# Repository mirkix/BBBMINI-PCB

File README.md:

# BBBMINI-PCB

## License

<br /><span xmlns:dct="http://purl.org/dc/terms/" property="dct:title">BBBmini</span> by <a xmlns:cc="http://creativecommons.org/ns#" href="https://github.com/mirkix" property="cc:attributionName" rel="cc:attributionURL">Mirko Denecke</a> is licensed under a <a rel="license" href="http://creativecommons.org/licenses/by-sa/4.0/">Creative Commons Attribution-ShareAlike 4.0 International License</a>.

UNLESS OTHERWISE MUTUALLY AGREED TO BY THE PARTIES IN WRITING, LICENSOR OFFERS THE WORK AS-IS AND MAKES NO REPRESENTATIONS OR WARRANTIES OF ANY KIND CONCERNING THE WORK, EXPRESS, IMPLIED, STATUTORY OR OTHERWISE, INCLUDING, WITHOUT LIMITATION, WARRANTIES OF TITLE, MERCHANTABILITY, FITNESS FOR A PARTICULAR PURPOSE, NONINFRINGEMENT, OR THE ABSENCE OF LATENT OR OTHER DEFECTS, ACCURACY, OR THE PRESENCE OF ABSENCE OF ERRORS, WHETHER OR NOT DISCOVERABLE. SOME JURISDICTIONS DO NOT ALLOW THE EXCLUSION OF IMPLIED WARRANTIES, SO SUCH EXCLUSION MAY NOT APPLY TO YOU. EXCEPT TO THE EXTENT REQUIRED BY APPLICABLE LAW, IN NO EVENT WILL LICENSOR BE LIABLE TO YOU ON ANY LEGAL THEORY FOR ANY SPECIAL, INCIDENTAL, CONSEQUENTIAL, PUNITIVE OR EXEMPLARY DAMAGES ARISING OUT OF THIS LICENSE OR THE USE OF THE WORK, EVEN IF LICENSOR HAS BEEN ADVISED OF THE POSSIBILITY OF SUCH DAMAGES.

## Changelog

Rev 1.5
* Add second I2C port
* Add current and voltage sensing
* Fix HC-SR04 voltage divider

Rev 1.4
* Add connector for Ultra Sonic Range Finder HC-SR04.
* Add 5V pin to P10 (GPS / UART4)
* Add 5V pin to P4 (RC Input)
* Add voltage divider to P4 (RC Input) pin RC_IN (RCIN) to connect 5V signals to RC_IN (RCIN)
* Add MPU-9250 interrupt singal to PRU0

Rev 1.2
* Initial commit

## BOM

### PCB

You can order BBBmini PCBs from OSHPARK https://oshpark.com/shared_projects/CtVQp1YO .

This is an example how you can get 10 BBBMINI-PCBs for less than 30$ at Shenthen2u.

Goto http://www.shenzhen2u.com/PCB 

Upload [bbbmini.zip](kicad/gerber/bbbmini.zip) to supplier.

Finish your order.

### IMU MPU-9250

Search for GY-9250 or MPU-9250 at [aliexpress](http://www.aliexpress.com/wholesale?SearchText=gy-9250)

### Baro MS5611

Search for GY-63 or MS5611 at [aliexpress](http://www.aliexpress.com/wholesale?SearchText=gy-63)

### Rangefinder HC-SR04

Search for HC-SR04, there are a lot of sellers.

## Connector

### P1 & P2
* 2.54mm pin header 3 x 12 straight or 90°
* 12 x RC out 3.3V

### P3
* 2.54 mm pin header 1 x 2 straight
* Close this jumper to connect 5V BBBMINI power supply to P1 / P2 RC out 5V

### P4 
* 2.54 mm pin header 1 x 4 straight
* RC receiver input. 
* For 5V RCIN signal R4 = 1kOhm and R5 = 2kOhm.
* For 3.3V RCIN signal R4 = 0Ohm / bridged and R5 = open / not equipped.

### P5
* 2.54mm pin header female 1 x 10 straight
* MPU-9250 breakout board

### P6
* 2.54mm pin header female 1 x 7 straight
* MS5611 breakout board

### P7
* 2.54mm pin header 1 x 5 straight
* UART4 port
* RX and TX 3.3V signals

### P8
* 2.54mm pin header 2 x 23 straight
* BeagleBone connector, pin header has to soldered on the back of the BBBMINI-PCB

### P9
* 2.54mm pin header 2 x 23 straight
* BeagleBone connector, pin header has to soldered on the back of the BBBMINI-PCB

### P10
* 2.54mm pin header 1 x 5 straight
* UART5 port (GPS)
* RX and TX 3.3V signals

### P11
* 2.54mm pin header 1 x 2 straight
* Connector for power supply. Use this connector to power the BeagleBone Black and BBBMIN-PCB. You can also use the BeagleBone Black power plug to power the BeagleBone Black and BBBMINI-PCB.

### P12
* 2.54mm pin header 1 x 7 straight
* External SPI Bus connector for additional hardware. 
* MOSI, MISO, SCLK and CS 3.3V

### P13
* 2.54mm pin header 1 x 2 straight
* CAN Bus interface

### P14
* 2.54mm pin header 1 x 2 straight
* Close this jumper to enable 120Ohm CAN Bus resistor.

### P15
* 2.54mm pin header 1 x 5 straight
* External I2C Bus  connector for additional hardware.
* SDA and SCL 3.3V

### P16
* 2.54mm pin header 1 x 3 straight
* Additional RC_1 ESC out connector for X-Quad configuration.
* RC_1 out 3.3V

### P17
* 2.54mm pin header 1 x 3 straight
* Additional RC_3 ESC out connector for X-Quad configuration.
* RC_3 out 3.3V

### P18
* 2.54mm pin header 1 x 3 straight
* Additional RC_4 ESC out connector for X-Quad configuration.
* RC_4 out 3.3V

### P19
* 2.54mm pin header 1 x 4 straight
* Ultrasonic Range Finder connector
* Connect HC-SR04 Range Finder here.  

### P20
* 2.54mm pin header 1 x 5 straight
* External I2C Bus  connector for additional hardware.
* SDA and SCL 3.3V

### P21
* 2.54mm pin header 1 x 3 straight
* Current and voltage sensing via Power Module

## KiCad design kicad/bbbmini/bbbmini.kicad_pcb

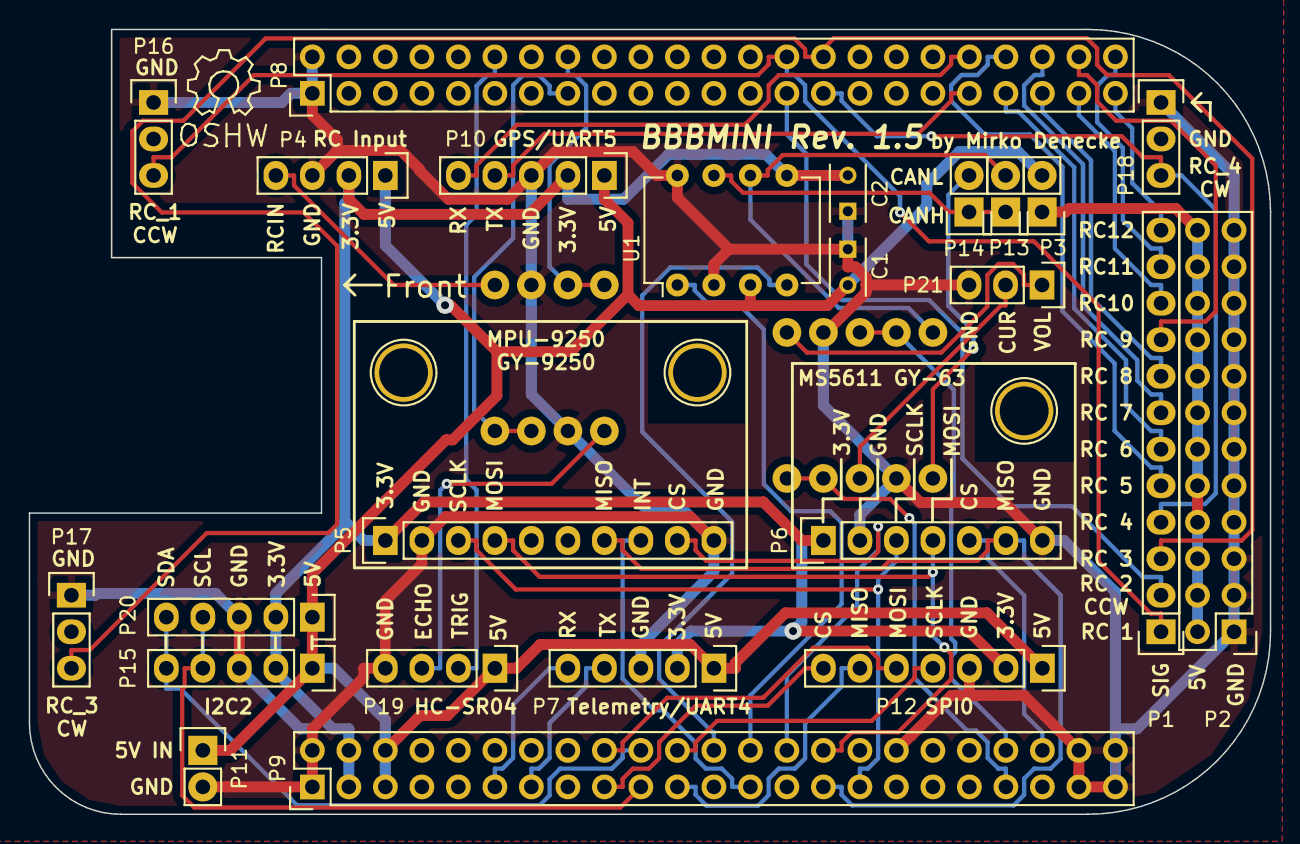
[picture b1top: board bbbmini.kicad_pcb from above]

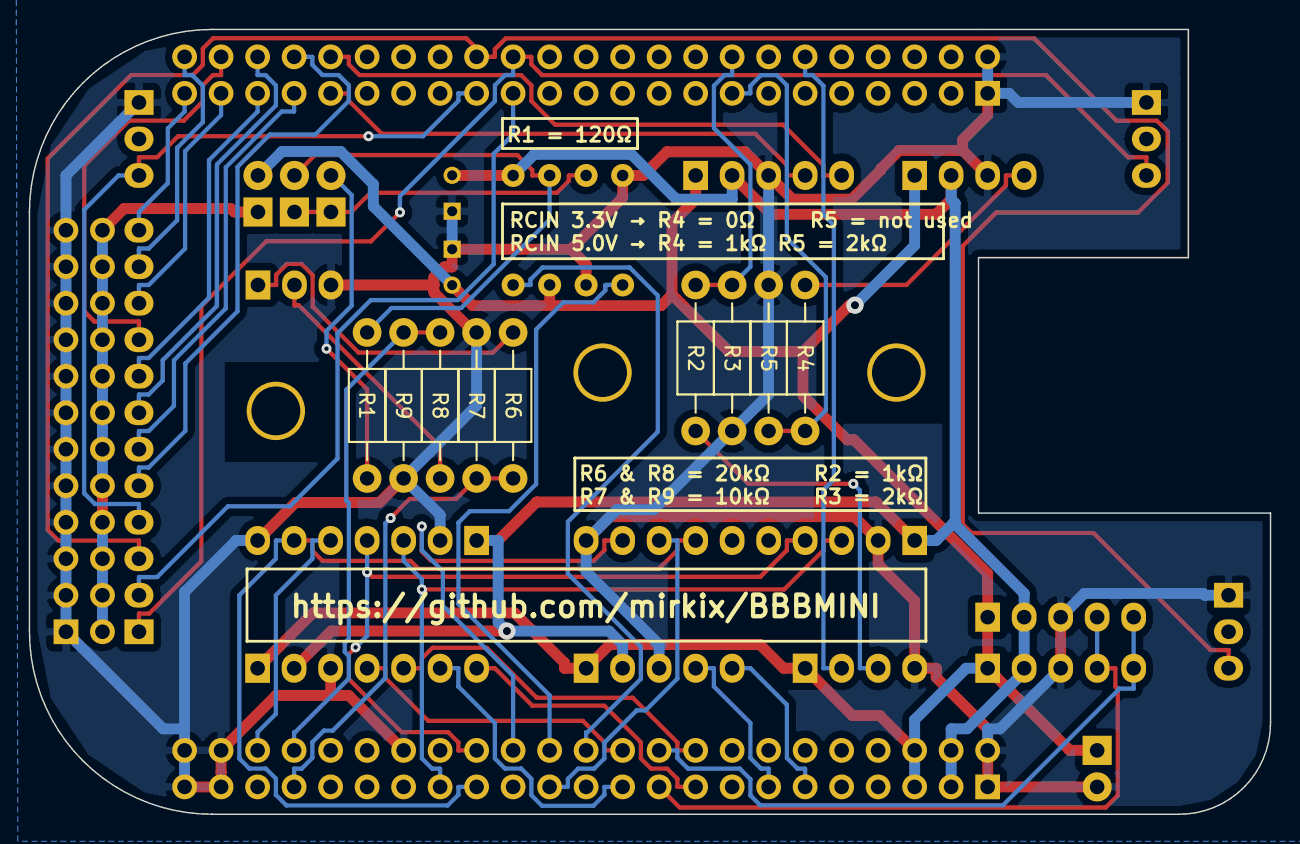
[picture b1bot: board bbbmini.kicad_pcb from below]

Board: 2 copper layers, 86.4 x 54.6 mm, 36 parts (9 on the bottom side), 46 nets.

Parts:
C1, C2: 0.1u; C_Rect_L4_W2.5_P2.5
P1: RC_OUTPUT; Pin_Header_Straight_1x12
P2: RC_OUTPUT_GND; Pin_Header_Straight_2x12
P3: 5V TO RC_OUT; Pin_Header_Straight_1x02
P4: RC_IN; Pin_Header_Straight_1x04
P5: MPU-9250 breakoutboard; Pin_Header_Straight_1x10
P6: MS5611 breakoutboard; Pin_Header_Straight_1x07
P7: Telemetry; Pin_Header_Straight_1x05
P8: BBB_P8; Pin_Header_Straight_2x23
P9: BBB_P9; Pin_Header_Straight_2x23
P10: GPS; Pin_Header_Straight_1x05
P11: 5V_INPUT; Pin_Header_Straight_1x02
P12: SPI0; Pin_Header_Straight_1x07
P13: CANBUS; Pin_Header_Straight_1x02
P14: CANBUS R; Pin_Header_Straight_1x02
P15, P20: I2C2; Pin_Header_Straight_1x05
P16: RC_1; Pin_Header_Straight_1x03
P17: RC_3; Pin_Header_Straight_1x03
P18: RC_4; Pin_Header_Straight_1x03
P19: HC_SR04; Pin_Header_Straight_1x04
P21: V / I; Pin_Header_Straight_1x03
R1: 120; Resistor_Horizontal_RM10mm
R2, R4: 1k; Resistor_Horizontal_RM10mm
R3, R5: 2k; Resistor_Horizontal_RM10mm
R6, R8: 20k; Resistor_Horizontal_RM10mm
R7, R9: 10k; Resistor_Horizontal_RM10mm
REF1, REF2, REF3: 1pin
U1: MCP2562; DIP-8_W7.62mm

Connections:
+3V3: C2.2, P4.2, P5.1, P6.1, P7.2, P9.3, P9.4, P10.2, P12.2, P15.2, P20.2, U1.5
+5V: C1.2, P3.2, P4.1, P7.1, P9.5, P9.6, P10.1, P11.1, P12.1, P15.1, P19.1, P20.1, U1.3
/CANH: P13.1, P14.1, U1.7
/CANL: P13.2, R1.2, U1.6
/CAN_RX: P9.24, U1.4
/CAN_TX: P9.26, U1.1
/CURRENT: P9.40, R8.2, R9.1
/GPS_RX: P8.37, P10.4
/GPS_TX: P8.38, P10.5
/I2C2_SCL: P9.19, P15.4, P20.4
/I2C2_SDA: P9.20, P15.5, P20.5
/MPU9250_INT: P5.8, P9.25
/RADIO_RX: P7.4, P9.13
/RADIO_TX: P7.5, P9.11
/RC_1: P1.1, P8.28, P16.3
/RC_2: P1.2, P8.27
/RC_3: P1.3, P8.30, P17.3
/RC_4: P1.4, P8.29, P18.3
/RC_5: P1.5, P8.40
/RC_6: P1.6, P8.39
/RC_7: P1.7, P8.42
/RC_8: P1.8, P8.41
/RC_9: P1.9, P8.44
/RC_10: P1.10, P8.43
/RC_11: P1.11, P8.46
/RC_12: P1.12, P8.45
/RC_IN: P8.15, R4.2, R5.1
/SPI0_CS: P9.17, P12.7
/SPI0_MISO: P9.21, P12.6
/SPI0_MOSI: P9.18, P12.5
/SPI0_SCLK: P9.22, P12.4
/SPI1_CS0: P5.9, P9.28
/SPI1_CS1: P6.5, P9.42
/SPI1_MISO: P5.7, P6.6, P9.29
/SPI1_MOSI: P5.4, P6.4, P9.30
/SPI1_SCLK: P5.3, P6.3, P9.31
/SR04_ECHO: P8.16, R2.2, R3.1
/SR04_TRIG: P8.12, P19.2
/VOLTAGE: P9.39, R6.2, R7.1
GND: C1.1, C2.1, P2.1, P2.3, P2.5, P2.7, P2.9, P2.11, P2.13, P2.15, P2.17, P2.19, P2.21, P2.23, P4.3, P5.2, P5.10, P6.2, P6.7, P7.3, P8.1, P8.2, P9.1, P9.2, P9.34, P9.43, P9.44, P9.45, P9.46, P10.3, P11.2, P12.3, P15.3, P16.1, P17.1, P18.1, P19.4, P20.3, P21.3, R3.2, R5.2, R7.2, R9.2, U1.2, U1.8
unnamed: P2.2, P2.4, P2.6, P2.8, P2.10, P2.12, P2.14, P2.16, P2.18, P2.20, P2.22, P2.24, P3.1
unnamed: P4.4, R4.1
unnamed: P14.2, R1.1
unnamed: P19.3, R2.1
unnamed: P21.1, R6.1
unnamed: P21.2, R8.1

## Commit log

2015-07-01 inital commit
2015-07-02 fix lib path
2015-07-05 move RC_2 & RC_4 to reduce footprint and protect esc/servo cables using 90 degree pinheader
2015-07-09 Rev 1.4
2015-07-11 Add Changelog
2015-07-11 Add BOM
2015-07-11 Add pcborder.png
2015-07-12 Add README.md for Gerber Files
2015-07-12 Put in table
2015-07-13 Add HC-SR04
2015-07-28 Modify ali link.
2015-07-31 Add connector description.
2015-08-05 Fix P7 & P10
2015-08-06 Add Rev 1.4 BOM
2015-08-06 fix formating
2015-09-15 Move case from BBBMINI to BBBMINI-PCB
2015-09-15 Add picture
2015-11-20 Add license
2016-01-03 add kicad 3d view screenshots
2016-02-15 Rev. 1.5
2016-02-15 Add Rev. 1.5 picture
2016-02-15 Add P20 and P21
2016-02-17 Updated BOM for 1.5 rev
    Added resistors for the new rev 1.5 boards
2016-02-18 Add tabs
2018-01-24 Add OSHPARK
